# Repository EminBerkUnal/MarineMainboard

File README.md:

Marine Main Deck Board
---------------------------------
Issued Date: 12 December 2023
Revision 1

This is a marine main deck controller board prototype I made for a commercial ship project that powered an HMI screen for performing general deck controls.

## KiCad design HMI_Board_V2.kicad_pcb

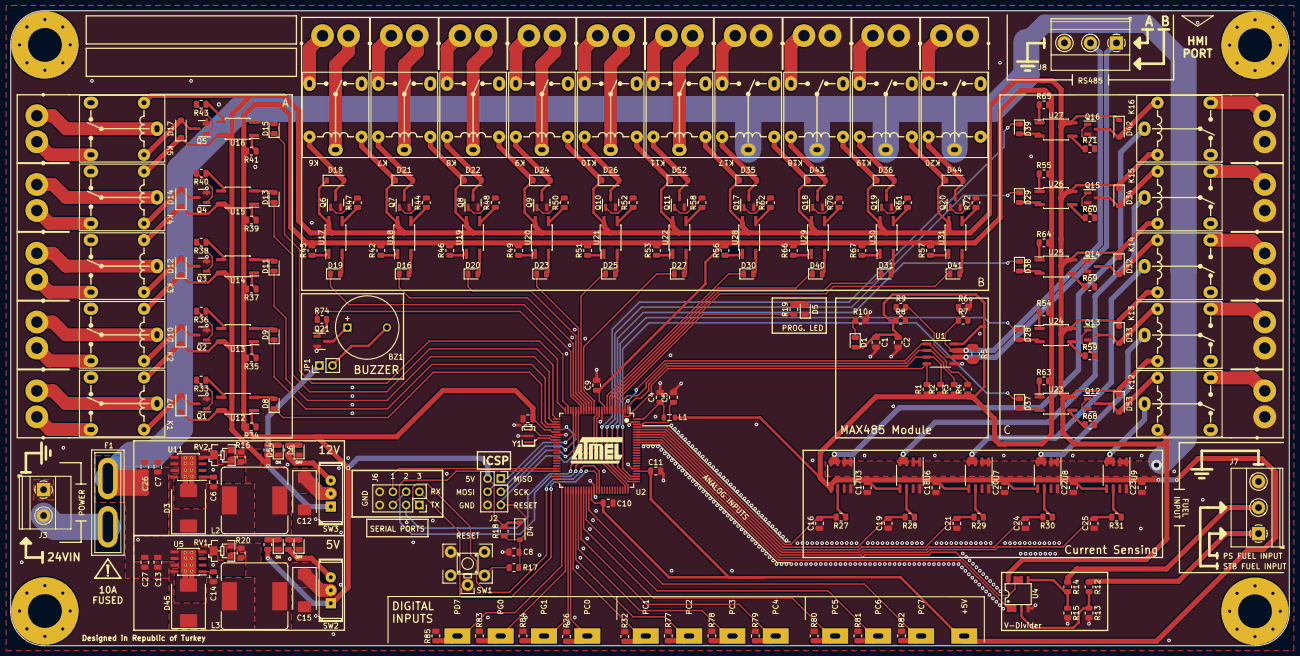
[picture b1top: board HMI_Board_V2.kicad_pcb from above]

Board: 2 copper layers, 245.8 x 122.1 mm, 301 parts (0 on the bottom side), 232 nets.

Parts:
BZ1: FT12095-G/12V; MagneticBuzzer_ProSignal_ABI-010-RC
C1: 10uF; C_0805_2012Metric
C2, C17, C18, C20, C22, C23: 0.1uF; C_0805_2012Metric
C3, C4, C5, C8, C9, C10, C11: 100nF; C_0805_2012Metric
C6, C14: 10nF; C_0805_2012Metric
C7, C13, C26, C27: CL21A475KAQNNNE; C_0805_2012Metric
C12, C15: 6TPB330M; CP_EIA-7343-31_Kemet-D
C16, C19, C21, C24, C25: 0.1nF; C_0805_2012Metric
D1, D2, D5, D8, D9, D11, D13, D15, D16, D19, D20, D23, D25, D27, D28, D29, D30, D31, D37, D38, D39, D40, D41, D54: KT-0805G; LED_0805_2012Metric
D3, D45: B540C-13-F; D_SMC
D4: BZT52C4V7; D_SOD-123
D6, D46: NCD0805R1; LED_0805_2012Metric
D7, D10, D12, D14, D17, D18, D21, D22, D24, D26, D32, D33, D34, D35, D36, D42, D43, D44, D52, D53: 1N4007; D_SOD-123
EDGE1, EDGE2, EDGE3, EDGE4: MountingHole_6.5mm_Pad_Via
F1: Fuse; Fuse_Blade_ATO_directSolder
G2: LOGO
J2: DS1023-2*3SF11; PinSocket_2x03_P2.54mm_Vertical
J3: DB128V-5.0-2P-OG-S; TerminalBlock_Phoenix_MKDS-1,5-2_1x02_P5.00mm_Horizontal
J5, J19, J20, J21, J23, J24, J25, J26, J28, J29, J30, J31: Conn_01x01_Pin; MountingHole_2.5mm_Pad
J6: DS1023-2*4SF11; PinSocket_2x04_P2.54mm_Vertical
J7, J8: DB128V-5.0-3P-OG-S; TerminalBlock_Phoenix_MKDS-1,5-3_1x03_P5.00mm_Horizontal
J9, J10, J11, J12, J13, J14, J15, J16, J17, J18, J32, J33, J34, J35, J36, J37, J38, J39, J40, J41, J42, J43, J44, J45, J46, J47, J48, J49, J50, J51, J52, J53, J54, J55, J56, J57, J58, J59, J60, J61: Conn_01x01_Pin; MountingHole_2.2mm_M2_Pad
JP1: Jumper_2_Bridged; PinHeader_1x02_P2.54mm_Vertical
K1, K2, K3, K4, K5, K6, K7, K8, K9, K10, K11, K12, K13, K14, K15, K16, K17, K18, K19, K20: SRA-12VDC-CL
L1: 10uH; L_0805_2012Metric
L2, L3: SRR1280-150M; L_Bourns_SRR1260
Q1, Q2, Q3, Q4, Q5, Q6, Q7, Q8, Q9, Q10, Q11, Q12, Q13, Q14, Q15, Q16, Q17, Q18, Q19, Q20, Q21: MMBT2222A 1P; SOT-23
R1, R2, R3, R4, R6, R7, R8, R9, R12, R13, R14, R15, R16, R18, R20: 10K; R_0805_2012Metric
R5: 120R; R_0805_2012Metric
R10, R11, R19, R23, R34, R35, R37, R39, R41, R42, R45, R46, R49, R51, R53, R54, R55, R56, R57, R63, R64, R65, R66, R67: 1K; R_0805_2012Metric
R17: 330R; R_0805_2012Metric
R24, R25: 2.4K; R_0805_2012Metric
R26, R32, R74, R77, R78, R79, R80, R81, R82, R83, R84, R85: 4.7K; R_0805_2012Metric
R27, R28, R29, R30, R31: 100R; R_0805_2012Metric
R33, R36, R38, R40, R43, R44, R47, R48, R50, R52, R58, R59, R60, R61, R62, R68, R69, R70, R71, R72: 510R; R_0805_2012Metric
RV1, RV2: TC33X-2-502E; SMD Potentiometer 3x3.8
SW1: SKHHQVA010; SKHHQVA010_Straight SPST
SW2, SW3: SS-12E19-G020; SPDT_3Pin_11.6x4.1_2.5mm_Straight
U1: MAX485ESA+T; SO-8_3.9x4.9mm_P1.27mm
U2: ATmega2560-16A; TQFP-100_14x14mm_P0.5mm
U3, U6, U7, U8, U9: CC6900SO-20A; SO-8_3.9x4.9mm_P1.27mm
U4: NE5532DR; LM358_SOIC-8_SMD
U5, U11: TPS5430DDAR; TI_SO-PowerPAD-8_ThermalVias
U12, U13, U14, U15, U16, U17, U18, U19, U20, U21, U22, U23, U24, U25, U26, U27, U28, U29, U30, U31: EL357N(B)(TA)-G; SO-4_4.4x3.6mm_P2.54mm
Y1: CSTNE16M0V53L000R0; Resonator_SMD_Murata_CSTxExxV-3Pin_3.0x1.1mm

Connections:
+5V: C1.1, C2.1, C3.1, C9.1, C10.1, C11.1, C17.2, C18.2, C20.2, C22.2, C23.2, D1.2 (A), D4.1 (K), J2.2, J31.1, L1.1, R1.1, R2.1, R3.1, R4.1, R8.1, R11.2, R18.2, R34.2, R35.2, R37.2, R39.2, R41.2, R42.2, R45.2, R46.2, R49.2, R51.2, R53.2, R54.2, R55.2, R56.2, R57.2, R63.2, R64.2, R65.2, R66.2, R67.2, SW2.1 (A), U1.8 (VCC), U2.10 (VCC), U2.31 (VCC), U2.61 (VCC), U2.80 (VCC), U3.5 (VCC), U6.5 (VCC), U7.5 (VCC), U8.5 (VCC), U9.5 (VCC)
+5VA: C4.1, L1.2, U2.100 (AVCC)
+12V: D7.1 (K), D10.1 (K), D12.1 (K), D14.1 (K), D17.1 (K), D18.1 (K), D21.1 (K), D22.1 (K), D24.1 (K), D26.1 (K), D32.1 (K), D33.1 (K), D34.1 (K), D35.1 (K), D36.1 (K), D42.1 (K), D43.1 (K), D44.1 (K), D52.1 (K), D53.1 (K), JP1.1 (A), K1.5, K2.5, K3.5, K4.5, K5.5, K6.5, K7.5, K8.5, K9.5, K10.5, K11.5, K12.5, K13.5, K14.5, K15.5, K16.5, K17.5, K18.5, K19.5, K20.5, R25.2, SW3.1 (A), U4.8 (V+), U12.4, U13.4, U14.4, U15.4, U16.4, U17.4, U18.4, U19.4, U20.4, U21.4, U22.4, U23.4, U24.4, U25.4, U26.4, U27.4, U28.4, U29.4, U30.4, U31.4
+24V: C7.1, C13.1, C26.1, C27.1, F1.2, K17.1, K18.1, K19.1, K20.1, U3.1 (IP+), U3.2 (IP+), U5.7 (VIN), U6.1 (IP+), U6.2 (IP+), U7.1 (IP+), U7.2 (IP+), U8.1 (IP+), U8.2 (IP+), U9.1 (IP+), U9.2 (IP+), U11.7 (VIN)
/ATMEGA2560/AREF: C5.1, U2.98 (AREF)
/ATMEGA2560/Buzz_N: BZ1.1, Q21.3 (C)
/ATMEGA2560/Buzz_P: BZ1.2, JP1.2 (B)
/ATMEGA2560/Buzz_T: Q21.1 (B), R74.2
/ATMEGA2560/PB1/SCK: J2.3, U2.20 (PB1)
/ATMEGA2560/PB2/MOSI: J2.4, U2.21 (PB2)
/ATMEGA2560/PB3/MISO: J2.1, U2.22 (PB3)
/ATMEGA2560/PB5: R74.1, U2.24 (PB5)
/ATMEGA2560/PC0: J5.1, R26.1, U2.53 (PC0)
/ATMEGA2560/PC1: J19.1, R32.1, U2.54 (PC1)
/ATMEGA2560/PC2: J20.1, R77.1, U2.55 (PC2)
/ATMEGA2560/PC3: J21.1, R78.1, U2.56 (PC3)
/ATMEGA2560/PC4: J23.1, R79.1, U2.57 (PC4)
/ATMEGA2560/PC5: J24.1, R80.1, U2.58 (PC5)
/ATMEGA2560/PC6: J25.1, R81.1, U2.59 (PC6)
/ATMEGA2560/PC7: J26.1, R82.1, U2.60 (PC7)
/ATMEGA2560/PD2/RX1: J6.6, U2.45 (PD2)
/ATMEGA2560/PD3/TX1: J6.5, U2.46 (PD3)
/ATMEGA2560/PD7: J30.1, R85.1, U2.50 (PD7)
/ATMEGA2560/PG0: J28.1, R83.1, U2.51 (PG0)
/ATMEGA2560/PG1: J29.1, R84.1, U2.52 (PG1)
/ATMEGA2560/PH0/RX2: J6.4, U2.12 (PH0)
/ATMEGA2560/PH1/TX2: J6.3, U2.13 (PH1)
/ATMEGA2560/PJ0/RX3: J6.2, U2.63 (PJ0)
/ATMEGA2560/PJ1/TX3: J6.1, U2.64 (PJ1)
/ATMEGA2560/PROG_LED: R19.1, U2.5 (PE3)
/ATMEGA2560/RESET: C8.1, D4.2 (A), J2.5, R17.2, R18.1, U2.30 (~RESET)
/ATMEGA2560/XTAL1: U2.34 (XTAL1), Y1.1
/ATMEGA2560/XTAL2: U2.33 (XTAL2), Y1.3
/Current Sensors/OUT1: R27.1, U3.6 (OUT)
/Current Sensors/OUT2: R28.1, U6.6 (OUT)
/Current Sensors/OUT3: R29.1, U7.6 (OUT)
/Current Sensors/OUT4: R30.1, U8.6 (OUT)
/Current Sensors/OUT5: R31.1, U9.6 (OUT)
/Fuel Measurement/PS_Fuel_(0-10V): J7.1, R12.1
/Fuel Measurement/STB_Fuel_(0-10V): J7.2, R14.1
/MAX485/MAX485_A: J8.1, R5.2, R9.2, U1.6 (A)
/MAX485/MAX485_B: J8.2, R5.1, R7.1, U1.7 (B)
/Power/5V_OFF: R23.2, SW2.3 (C)
/Power/5V_REGOUT: C15.1, L3.2, R20.2, SW2.2 (B)
/Power/12V_OFF: R24.2, SW3.3 (C)
/Power/12V_REGOUT: C12.1, L2.2, R16.2, SW3.2 (B)
/Power/BOOT_C: C14.1, U5.1 (BOOT)
/Power/BOOT_R: C6.1, U11.1 (BOOT)
/Power/PH_C: C14.2, D45.1 (K), L3.1, U5.8 (PH)
/Power/PH_R: C6.2, D3.1 (K), L2.1, U11.8 (PH)
/Power/VSENSE_C: R20.1, RV1.1, RV1.2, U5.4 (VSENSE)
/Power/VSENSE_R: R16.1, RV2.1, RV2.2, U11.4 (VSENSE)
/Relays 1/OPT1: D8.2 (A), U12.2
/Relays 1/OPT2: D9.2 (A), U13.2
/Relays 1/OPT3: D11.2 (A), U14.2
/Relays 1/OPT4: D13.2 (A), U15.2
/Relays 1/OPT5: D15.2 (A), U16.2
/Relays 1/OPT6: D19.2 (A), U17.2
/Relays 1/OPT7: D16.2 (A), U18.2
/Relays 1/OPT8: D20.2 (A), U19.2
/Relays 1/OPT9: D23.2 (A), U20.2
/Relays 1/OPT10: D25.2 (A), U21.2
/Relays 1/RL1_C: J46.1, K1.1
/Relays 1/RL1_O: J9.1, K1.2
/Relays 1/RL2_C: J47.1, K2.1
/Relays 1/RL2_O: J10.1, K2.2
/Relays 1/RL3_C: J48.1, K3.1
/Relays 1/RL3_O: J11.1, K3.2
/Relays 1/RL4_C: J49.1, K4.1
/Relays 1/RL4_O: J12.1, K4.2
/Relays 1/RL5_C: J55.1, K5.1
/Relays 1/RL5_O: J13.1, K5.2
/Relays 1/RL6_C: J56.1, K6.1
/Relays 1/RL6_O: J14.1, K6.2
/Relays 1/RL7_C: J57.1, K7.1
/Relays 1/RL7_O: J15.1, K7.2
/Relays 1/RL8_C: J58.1, K8.1
/Relays 1/RL8_O: J16.1, K8.2
/Relays 1/RL9_C: J59.1, K9.1
/Relays 1/RL9_O: J17.1, K9.2
/Relays 1/RL10_C: J60.1, K10.1
/Relays 1/RL10_O: J18.1, K10.2
/Relays 2/OPT11: D27.2 (A), U22.2
/Relays 2/OPT12: D37.2 (A), U23.2
/Relays 2/OPT13: D28.2 (A), U24.2
/Relays 2/OPT14: D38.2 (A), U25.2
/Relays 2/OPT15: D29.2 (A), U26.2
/Relays 2/OPT16: D39.2 (A), U27.2
/Relays 2/OPT17: D30.2 (A), U28.2
/Relays 2/OPT18: D40.2 (A), U29.2
/Relays 2/OPT19: D31.2 (A), U30.2
/Relays 2/OPT20: D41.2 (A), U31.2
/Relays 2/RL11_C: J39.1, K11.1
/Relays 2/RL11_O: J32.1, K11.2
/Relays 2/RL12_O: J61.1, K12.2
/Relays 2/RL13_O: J33.1, K13.2
/Relays 2/RL14_O: J34.1, K14.2
/Relays 2/RL15_O: J35.1, K15.2
/Relays 2/RL16_O: J36.1, K16.2
/Relays 2/RL17_O: J37.1, K17.2
/Relays 2/RL18_O: J38.1, K18.2
/Relays 2/RL19_O: J53.1, K19.2
/Relays 2/RL20_O: J54.1, K20.2
Analog_Current1: C25.2, R31.2, U2.93 (PF4)
Analog_Current2: C24.2, R30.2, U2.94 (PF3)
Analog_Current3: C21.2, R29.2, U2.95 (PF2)
Analog_Current4: C19.2, R28.2, U2.96 (PF1)
Analog_Current5: C16.2, R27.2, U2.97 (PF0)
Current_Out1: K12.1, U9.3 (IP-), U9.4 (IP-)
Current_Out2: K13.1, U8.3 (IP-), U8.4 (IP-)
Current_Out3: K14.1, U7.3 (IP-), U7.4 (IP-)
Current_Out4: K15.1, U6.3 (IP-), U6.4 (IP-)
Current_Out5: K16.1, U3.3 (IP-), U3.4 (IP-)
GND: C1.2, C2.2, C3.2, C4.2, C5.2, C7.2, C8.2, C9.2, C10.2, C11.2, C12.2, C13.2, C15.2, C16.1, C17.1, C18.1, C19.1, C20.1, C21.1, C22.1, C23.1, C24.1, C25.1, C26.2, C27.2, D2.1 (K), D3.2 (A), D5.1 (K), D6.1 (K), D45.2 (A), D46.1 (K), D54.1 (K), J2.6, J3.1, J6.7, J6.8, J7.3, J8.3, J40.1, J41.1, J42.1, J43.1, J44.1, J45.1, J50.1, J51.1, J52.1, Q1.2 (E), Q2.2 (E), Q3.2 (E), Q4.2 (E), Q5.2 (E), Q6.2 (E), Q7.2 (E), Q8.2 (E), Q9.2 (E), Q10.2 (E), Q11.2 (E), Q12.2 (E), Q13.2 (E), Q14.2 (E), Q15.2 (E), Q16.2 (E), Q17.2 (E), Q18.2 (E), Q19.2 (E), Q20.2 (E), Q21.2 (E), R6.2, R10.2, R13.2, R15.2, R26.2, R32.2, R77.2, R78.2, R79.2, R80.2, R81.2, R82.2, R83.2, R84.2, R85.2, RV1.3, RV2.3, SW1.4, SW1.5, U1.5 (GND), U2.11 (GND), U2.32 (GND), U2.62 (GND), U2.81 (GND), U2.99 (GND), U3.8 (GND), U4.4 (V-), U5.5 (EN), U5.6 (GND), U5.9 (GNDPAD), U6.8 (GND), U7.8 (GND), U8.8 (GND), U9.8 (GND), U11.5 (EN), U11.6 (GND), U11.9 (GNDPAD), Y1.2
MAX485_DE: R2.2, U1.3 (DE), U2.1 (PG5)
MAX485_DI: R1.2, U1.4 (DI), U2.3 (PE1)
MAX485_RE: R3.2, U1.2 (~RE), U2.4 (PE2)
MAX485_RO: R4.2, U1.1 (RO), U2.2 (PE0)
unnamed: D1.1 (K), R10.1
unnamed: D2.2 (A), R11.1
unnamed: D5.2 (A), R19.2
unnamed: D6.2 (A), R24.1
unnamed: D7.2 (A), K1.4, Q1.3 (C)
unnamed: D10.2 (A), K2.4, Q2.3 (C)
unnamed: D12.2 (A), K3.4, Q3.3 (C)
unnamed: D14.2 (A), K4.4, Q4.3 (C)
unnamed: D17.2 (A), K5.4, Q5.3 (C)
unnamed: D18.2 (A), K6.4, Q6.3 (C)
unnamed: D21.2 (A), K7.4, Q7.3 (C)
unnamed: D22.2 (A), K8.4, Q8.3 (C)
unnamed: D24.2 (A), K9.4, Q9.3 (C)
unnamed: D26.2 (A), K10.4, Q10.3 (C)
unnamed: D32.2 (A), K14.4, Q14.3 (C)
unnamed: D33.2 (A), K13.4, Q13.3 (C)
unnamed: D34.2 (A), K15.4, Q15.3 (C)
unnamed: D35.2 (A), K17.4, Q17.3 (C)
unnamed: D36.2 (A), K19.4, Q19.3 (C)
unnamed: D42.2 (A), K16.4, Q16.3 (C)
unnamed: D43.2 (A), K18.4, Q18.3 (C)
unnamed: D44.2 (A), K20.4, Q20.3 (C)
unnamed: D46.2 (A), R23.1
unnamed: D52.2 (A), K11.4, Q11.3 (C)
unnamed: D53.2 (A), K12.4, Q12.3 (C)
unnamed: D54.2 (A), R25.1
unnamed: Q1.1 (B), R33.2
unnamed: Q2.1 (B), R36.2
unnamed: Q3.1 (B), R38.2
unnamed: Q4.1 (B), R40.2
unnamed: Q5.1 (B), R43.2
unnamed: Q6.1 (B), R47.2
unnamed: Q7.1 (B), R44.2
unnamed: Q8.1 (B), R48.2
unnamed: Q9.1 (B), R50.2
unnamed: Q10.1 (B), R52.2
unnamed: Q11.1 (B), R58.2
unnamed: Q12.1 (B), R68.2
unnamed: Q13.1 (B), R59.2
unnamed: Q14.1 (B), R69.2
unnamed: Q15.1 (B), R60.2
unnamed: Q16.1 (B), R71.2
unnamed: Q17.1 (B), R62.2
unnamed: Q18.1 (B), R70.2
unnamed: Q19.1 (B), R61.2
unnamed: Q20.1 (B), R72.2
unnamed: R6.1, R7.2
unnamed: R8.2, R9.1
unnamed: R17.1, SW1.2
unnamed: R33.1, U12.3
unnamed: R34.1, U12.1
unnamed: R35.1, U13.1
unnamed: R36.1, U13.3
unnamed: R37.1, U14.1
unnamed: R38.1, U14.3
unnamed: R39.1, U15.1
unnamed: R40.1, U15.3
unnamed: R41.1, U16.1
unnamed: R42.1, U18.1
unnamed: R43.1, U16.3
unnamed: R44.1, U18.3
unnamed: R45.1, U17.1
unnamed: R46.1, U19.1
unnamed: R47.1, U17.3
unnamed: R48.1, U19.3
unnamed: R49.1, U20.1
unnamed: R50.1, U20.3
unnamed: R51.1, U21.1
unnamed: R52.1, U21.3
unnamed: R53.1, U22.1
unnamed: R54.1, U24.1
unnamed: R55.1, U26.1
unnamed: R56.1, U28.1
unnamed: R57.1, U31.1
unnamed: R58.1, U22.3
unnamed: R59.1, U24.3
unnamed: R60.1, U26.3
unnamed: R61.1, U30.3
unnamed: R62.1, U28.3
unnamed: R63.1, U23.1
unnamed: R64.1, U25.1
unnamed: R65.1, U27.1
unnamed: R66.1, U29.1
unnamed: R67.1, U30.1
unnamed: R68.1, U23.3
unnamed: R69.1, U25.3
unnamed: R70.1, U29.3
unnamed: R71.1, U27.3
unnamed: R72.1, U31.3
unnamed: R12.2, R13.1, U4.3 (+)
unnamed: R14.2, R15.1, U4.5 (+)
PA0: D37.1 (K), U2.78 (PA0)
PA1: D28.1 (K), U2.77 (PA1)
PA2: D38.1 (K), U2.76 (PA2)
PA3: D29.1 (K), U2.75 (PA3)
PA4: D39.1 (K), U2.74 (PA4)
PB0: D19.1 (K), U2.19 (PB0)
PB6: D15.1 (K), U2.25 (PB6)
PB7: D13.1 (K), U2.26 (PB7)
PE4: D41.1 (K), U2.6 (PE4)
PE5: D31.1 (K), U2.7 (PE5)
PE6: D40.1 (K), U2.8 (PE6)
PE7: D30.1 (K), U2.9 (PE7)
PG3: D9.1 (K), U2.28 (PG3)
PG4: D8.1 (K), U2.29 (PG4)
PH2: D27.1 (K), U2.14 (PH2)
PH3: D25.1 (K), U2.15 (PH3)
PH4: D23.1 (K), U2.16 (PH4)
PH5: D20.1 (K), U2.17 (PH5)
PH6: D16.1 (K), U2.18 (PH6)
PH7: D11.1 (K), U2.27 (PH7)
PS_Fuel_(0-5V): U2.91 (PF6), U4.1, U4.2 (-)
Relay_Fuse: F1.1, J3.2
STB_Fuel_(0-5V): U2.92 (PF5), U4.6 (-), U4.7
